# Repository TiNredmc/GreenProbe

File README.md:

# GreenProbe

GreenProbe is the reverse-engineered version of SLG4DVKGSD I2C programmer for GreenPAK.

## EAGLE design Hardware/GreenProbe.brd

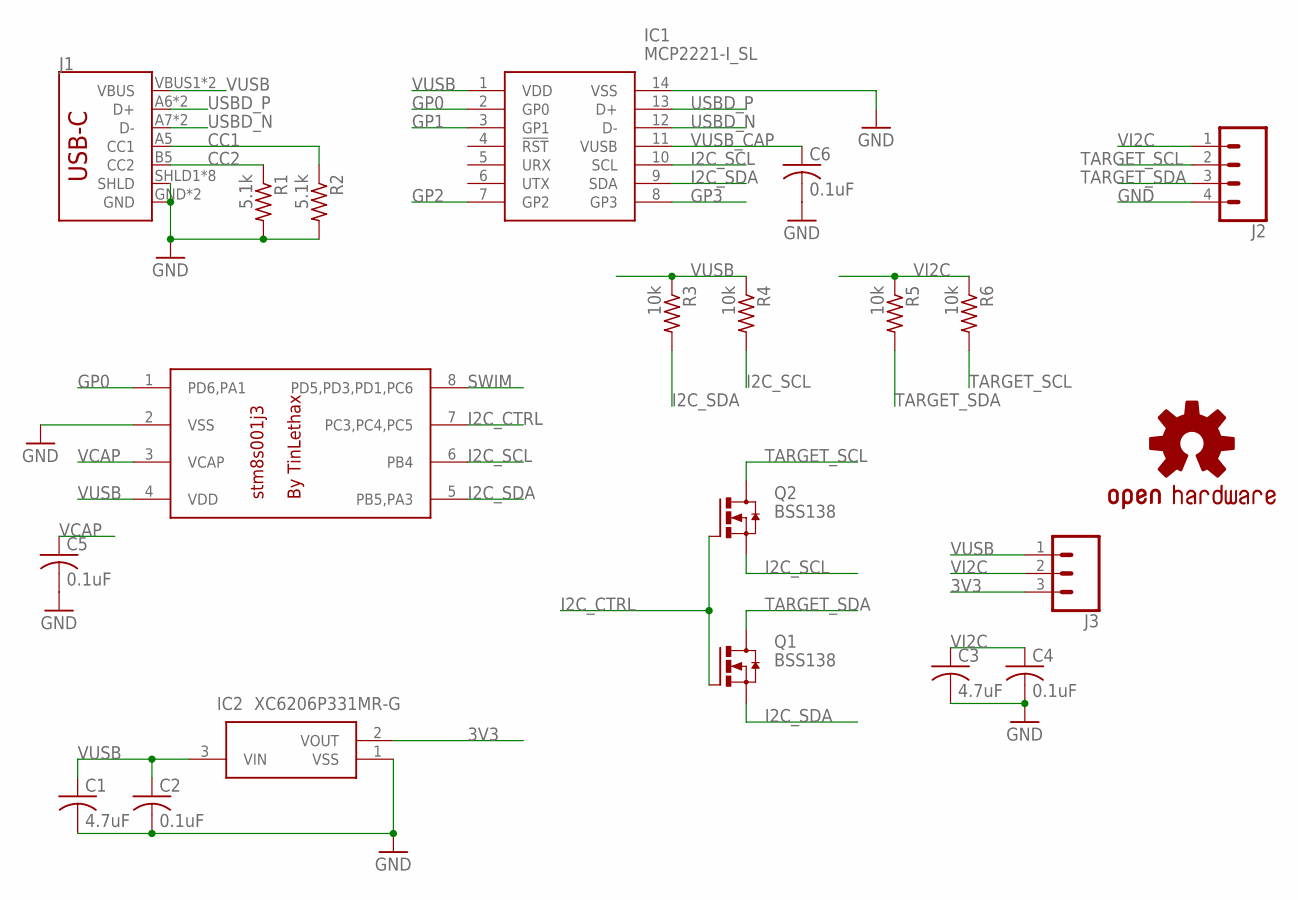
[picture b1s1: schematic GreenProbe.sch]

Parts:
C1, C3: 4.7uF; C0603
C2, C4, C5, C6: 0.1uF; C0603
IC1: MCP2221-I_SL; SOIC127P600X175-14N
IC2: XC6206P331MR-G; SOT95P280X130-3N
IC3: STM8S001J3; SOP8
J1: SPARKFUN-CONNECTORS_USB_C16PIN; SPARKFUN-CONNECTORS_USB-C-16P
J2: CONN_041X04_NO_SILK; 1X04_NO_SILK
J3: CONN_031X03_NO_SILK; 1X03_NO_SILK
LOGO1: OSHW-LOGOMINI; OSHW-LOGO-MINI
Q1, Q2: BSS138; SOT23-3
R1, R2: 5.1k; R0603
R3, R4, R5, R6: 10k; R0603

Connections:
3V3: IC2.2 (VOUT), J3.3
CC1: J1.A5 (CC1), R2.1
CC2: J1.B5 (CC2), R1.1
GND: C1.2, C2.2, C3.2, C4.2, C5.2, C6.2, IC1.14 (VSS), IC2.1 (VSS), IC3.2 (VSS), J1.GND, J1.GND2 (GND), J1.SHLD1 (SHLD), J1.SHLD2 (SHLD), J1.SHLD3 (SHLD), J1.SHLD4 (SHLD), J1.SHLD5 (SHLD), J1.SHLD6 (SHLD), J1.SHLD7 (SHLD), J1.SHLD8 (SHLD), J2.4, R1.2, R2.2
GP0: IC1.2 (GP0), IC3.1 (PD6,PA1)
GP1: IC1.3 (GP1)
GP2: IC1.7 (GP2)
GP3: IC1.8 (GP3)
I2C_CTRL: IC3.7 (PC3,PC4,PC5), Q1.1 (G), Q2.1 (G)
I2C_SCL: IC1.10 (SCL), IC3.6 (PB4), Q2.2 (S), R4.2
I2C_SDA: IC1.9 (SDA), IC3.5 (PB5,PA3), Q1.2 (S), R3.2
SWIM: IC3.8 (PD5,PD3,PD1,PC6)
TARGET_SCL: J2.2, Q2.3 (D), R6.2
TARGET_SDA: J2.3, Q1.3 (D), R5.2
USBD_N: IC1.12 (D-), J1.A7 (D-), J1.B7 (D-)
USBD_P: IC1.13 (D+), J1.A6 (D+), J1.B6 (D+)
VCAP: C5.1, IC3.3 (VCAP)
VI2C: C3.1, C4.1, J2.1, J3.2, R5.1, R6.1
VUSB: C1.1, C2.1, IC1.1 (VDD), IC2.3 (VIN), IC3.4 (VDD), J1.VBUS1 (VBUS), J1.VBUS2 (VBUS), J3.1, R3.1, R4.1
VUSB_CAP: C6.1, IC1.11 (VUSB)

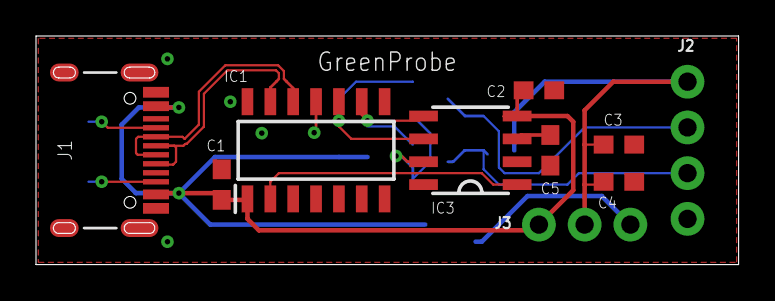
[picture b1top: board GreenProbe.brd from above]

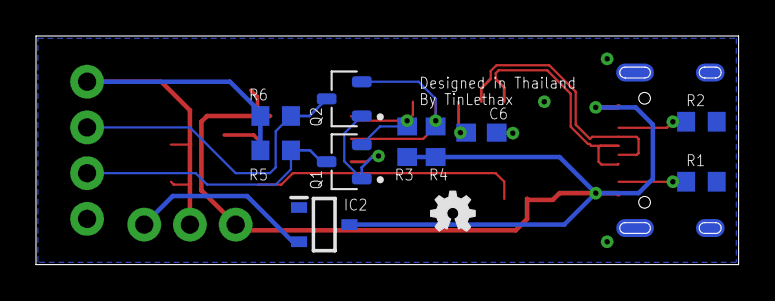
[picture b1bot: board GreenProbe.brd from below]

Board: 2 copper layers, 39.0 x 12.7 mm, 21 parts (11 on the bottom side), 16 nets.

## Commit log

2023-06-16 Initial.
2023-06-16 Create LICENSE

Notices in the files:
parts and their libraries:
SparkFun-Connectors: Licensing: Creative Commons ShareAlike 4.0 International - https://creativecommons.org/licenses/by-sa/4.0
